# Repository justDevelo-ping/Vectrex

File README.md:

# Vectrex
 In here, we will find all the work i've done to make more customization and reproduction of the vectrex arcade system available.

Kailh LP Modern Vectrex Controller © 2024 by Francis Olivier Houle is licensed under CC BY-NC 4.0. To view a copy of this license, visit https://creativecommons.org/licenses/by-nc/4.0/

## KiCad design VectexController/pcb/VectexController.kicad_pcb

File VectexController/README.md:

# Vectrex Controller v1.0
 This is the v0.1 of my controller including le PCB.
 
 - Possible Issues :
	- The joystick might be too big and prevent closing the remote inside he vectrex like the original intended
	
The controller is builded by staying fidele to the BOM of the original vectrex controller with part still in production. With the original schematic, the controller joystick is planned to work with 2.4v wich make it hit all the boxes on the test cartridge. a higher voltage Schemetic will be made later.

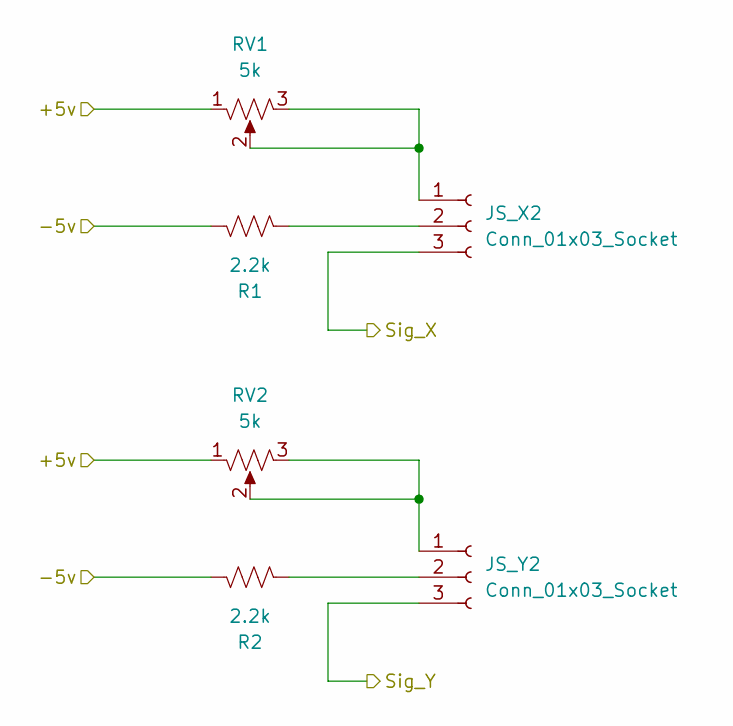
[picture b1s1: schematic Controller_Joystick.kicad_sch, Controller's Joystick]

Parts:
JS_X2: Conn_01x03_Socket; JST_XH_B3B-XH-A_1x03_P2.50mm_Vertical
JS_Y2: Conn_01x03_Socket; JST_XH_B3B-XH-A_1x03_P2.50mm_Vertical
R1, R2: 2.2k; R_Axial_DIN0207_L6.3mm_D2.5mm_P10.16mm_Horizontal
RV1, RV2: 5k; Potentiometer_Bourns_3296W_Vertical

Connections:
/Controller_Joystick/+5v: RV1.1, RV2.1; also elsewhere on the board
/Controller_Joystick/-5v: R1.1, R2.1; also elsewhere on the board
/Controller_Joystick/Sig_X: JS_X2.3; also elsewhere on the board
/Controller_Joystick/Sig_Y: JS_Y2.3; also elsewhere on the board
unnamed: JS_X2.1, RV1.2, RV1.3
unnamed: JS_X2.2, R1.2
unnamed: JS_Y2.1, RV2.2, RV2.3
unnamed: JS_Y2.2, R2.2

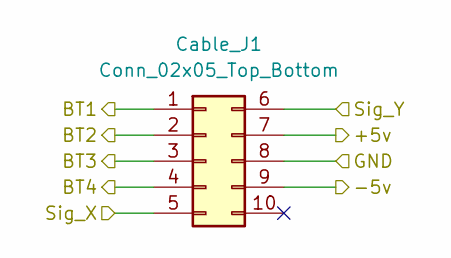
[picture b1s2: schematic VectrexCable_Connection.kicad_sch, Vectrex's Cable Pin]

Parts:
Cable_J1: Conn_02x05_Top_Bottom; PinHeader_2x05_P2.54mm_Horizontal

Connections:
/Controller_Button/BT1: Cable_J1.1; also elsewhere on the board
/Controller_Button/BT2: Cable_J1.2; also elsewhere on the board
/Controller_Button/BT3: Cable_J1.3; also elsewhere on the board
/Controller_Button/BT4: Cable_J1.4; also elsewhere on the board
/Controller_Button/GND: Cable_J1.8; also elsewhere on the board
/Controller_Joystick/+5v: Cable_J1.7; also elsewhere on the board
/Controller_Joystick/-5v: Cable_J1.9; also elsewhere on the board
/Controller_Joystick/Sig_X: Cable_J1.5; also elsewhere on the board
/Controller_Joystick/Sig_Y: Cable_J1.6; also elsewhere on the board

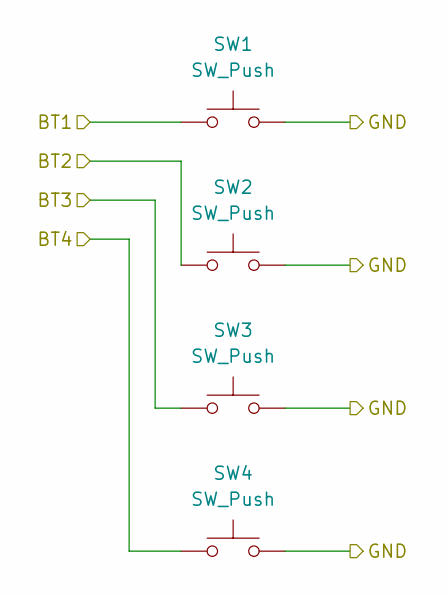
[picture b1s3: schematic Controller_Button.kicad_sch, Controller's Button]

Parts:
SW1, SW2, SW3, SW4: SW_Push; Kailh_socket_PG1350_optional

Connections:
/Controller_Button/BT1: SW1.1; also elsewhere on the board
/Controller_Button/BT2: SW2.1; also elsewhere on the board
/Controller_Button/BT3: SW3.1; also elsewhere on the board
/Controller_Button/BT4: SW4.1; also elsewhere on the board
/Controller_Button/GND: SW1.2, SW2.2, SW3.2, SW4.2; also elsewhere on the board

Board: 2 copper layers, 11 parts (0 on the bottom side), 13 nets, no tracks yet.

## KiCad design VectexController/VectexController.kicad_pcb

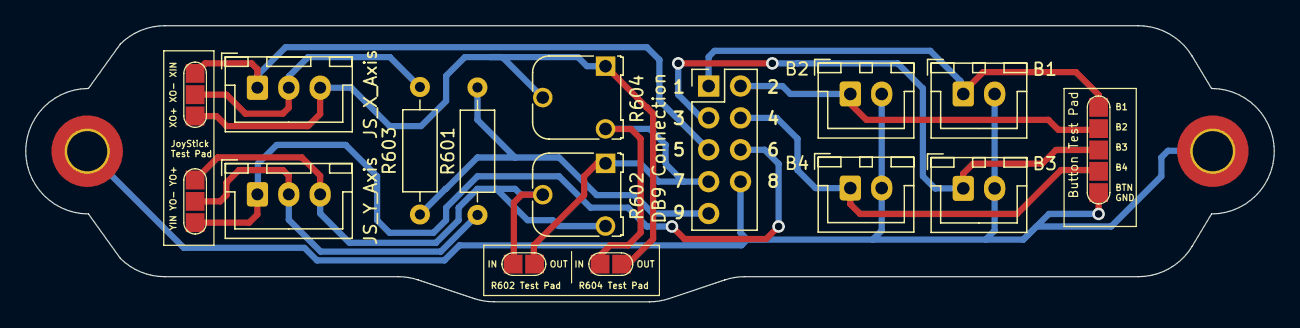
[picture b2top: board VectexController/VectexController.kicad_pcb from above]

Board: 2 copper layers, 99.5 x 22.0 mm, 18 parts (0 on the bottom side), 13 nets.

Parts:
B1: SW_Push1; JST_XH_B2B-XH-A_1x02_P2.50mm_Vertical
B2: SW_Push2; JST_XH_B2B-XH-A_1x02_P2.50mm_Vertical
B3: SW_Push3; JST_XH_B2B-XH-A_1x02_P2.50mm_Vertical
B4: SW_Push4; JST_XH_B2B-XH-A_1x02_P2.50mm_Vertical
Button Test Pad : TestPoint_Pad_1.5x1.5mm_x5
DB9 Connection: Conn_2Rows-09Pins; PinHeader_2x05_P2.54mm_Vertical
IN           OUT: TestPoint_Pad_1.5x1.5mm_x2
IN           OUT#2: TestPoint_Pad_1.5x1.5mm_x2
JS_X_Axis: 3Pins; JST_XH_B3B-XH-A_1x03_P2.50mm_Vertical
JS_Y_Axis: 3Pins; JST_XH_B3B-XH-A_1x03_P2.50mm_Vertical
MntHole1, MntHole2: MountingHole_3.2mm_M3_ISO7380_Pad_TopOnly
R601, R603: 4.7k; R_Axial_DIN0207_L6.3mm_D2.5mm_P10.16mm_Horizontal
R602, R604: 10k; Potentiometer_Runtron_RM-065_Vertical
XO+ XO- XIN: TestPoint_Pad_1.5x1.5mm_x3
YIN YO- YO+: TestPoint_Pad_1.5x1.5mm_x3

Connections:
unnamed: B1.1, Button Test Pad.1, DB9 Connection.1
unnamed: B2.1, Button Test Pad.2, DB9 Connection.2
unnamed: B3.1, Button Test Pad.3, DB9 Connection.3
unnamed: B4.1, Button Test Pad.4, DB9 Connection.4
unnamed: DB9 Connection.5, JS_X_Axis.1, XO+ XO- XIN.1
unnamed: DB9 Connection.6, JS_Y_Axis.1, YIN YO- YO+.1
unnamed: DB9 Connection.7, IN OUT.2, IN OUT#2.2, R602.1, R604.3
unnamed: B1.2, B2.2, B3.2, B4.2, Button Test Pad.5, DB9 Connection.8, MntHole1.1, MntHole2.1
unnamed: DB9 Connection.9, R601.2, R603.2
unnamed: JS_X_Axis.2, R603.1, XO+ XO- XIN.2
unnamed: IN OUT.1, JS_X_Axis.3, R604.1, R604.2, XO+ XO- XIN.3
unnamed: JS_Y_Axis.2, R601.1, YIN YO- YO+.2
unnamed: IN OUT#2.1, JS_Y_Axis.3, R602.2, R602.3, YIN YO- YO+.3

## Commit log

2024-08-31 File Managing and addition
    This include the works so far in my Creation of Vectrex controller
2024-08-31 Update LICENSE
    Change to the right licenses to stay opensource but prevent commercial use.
